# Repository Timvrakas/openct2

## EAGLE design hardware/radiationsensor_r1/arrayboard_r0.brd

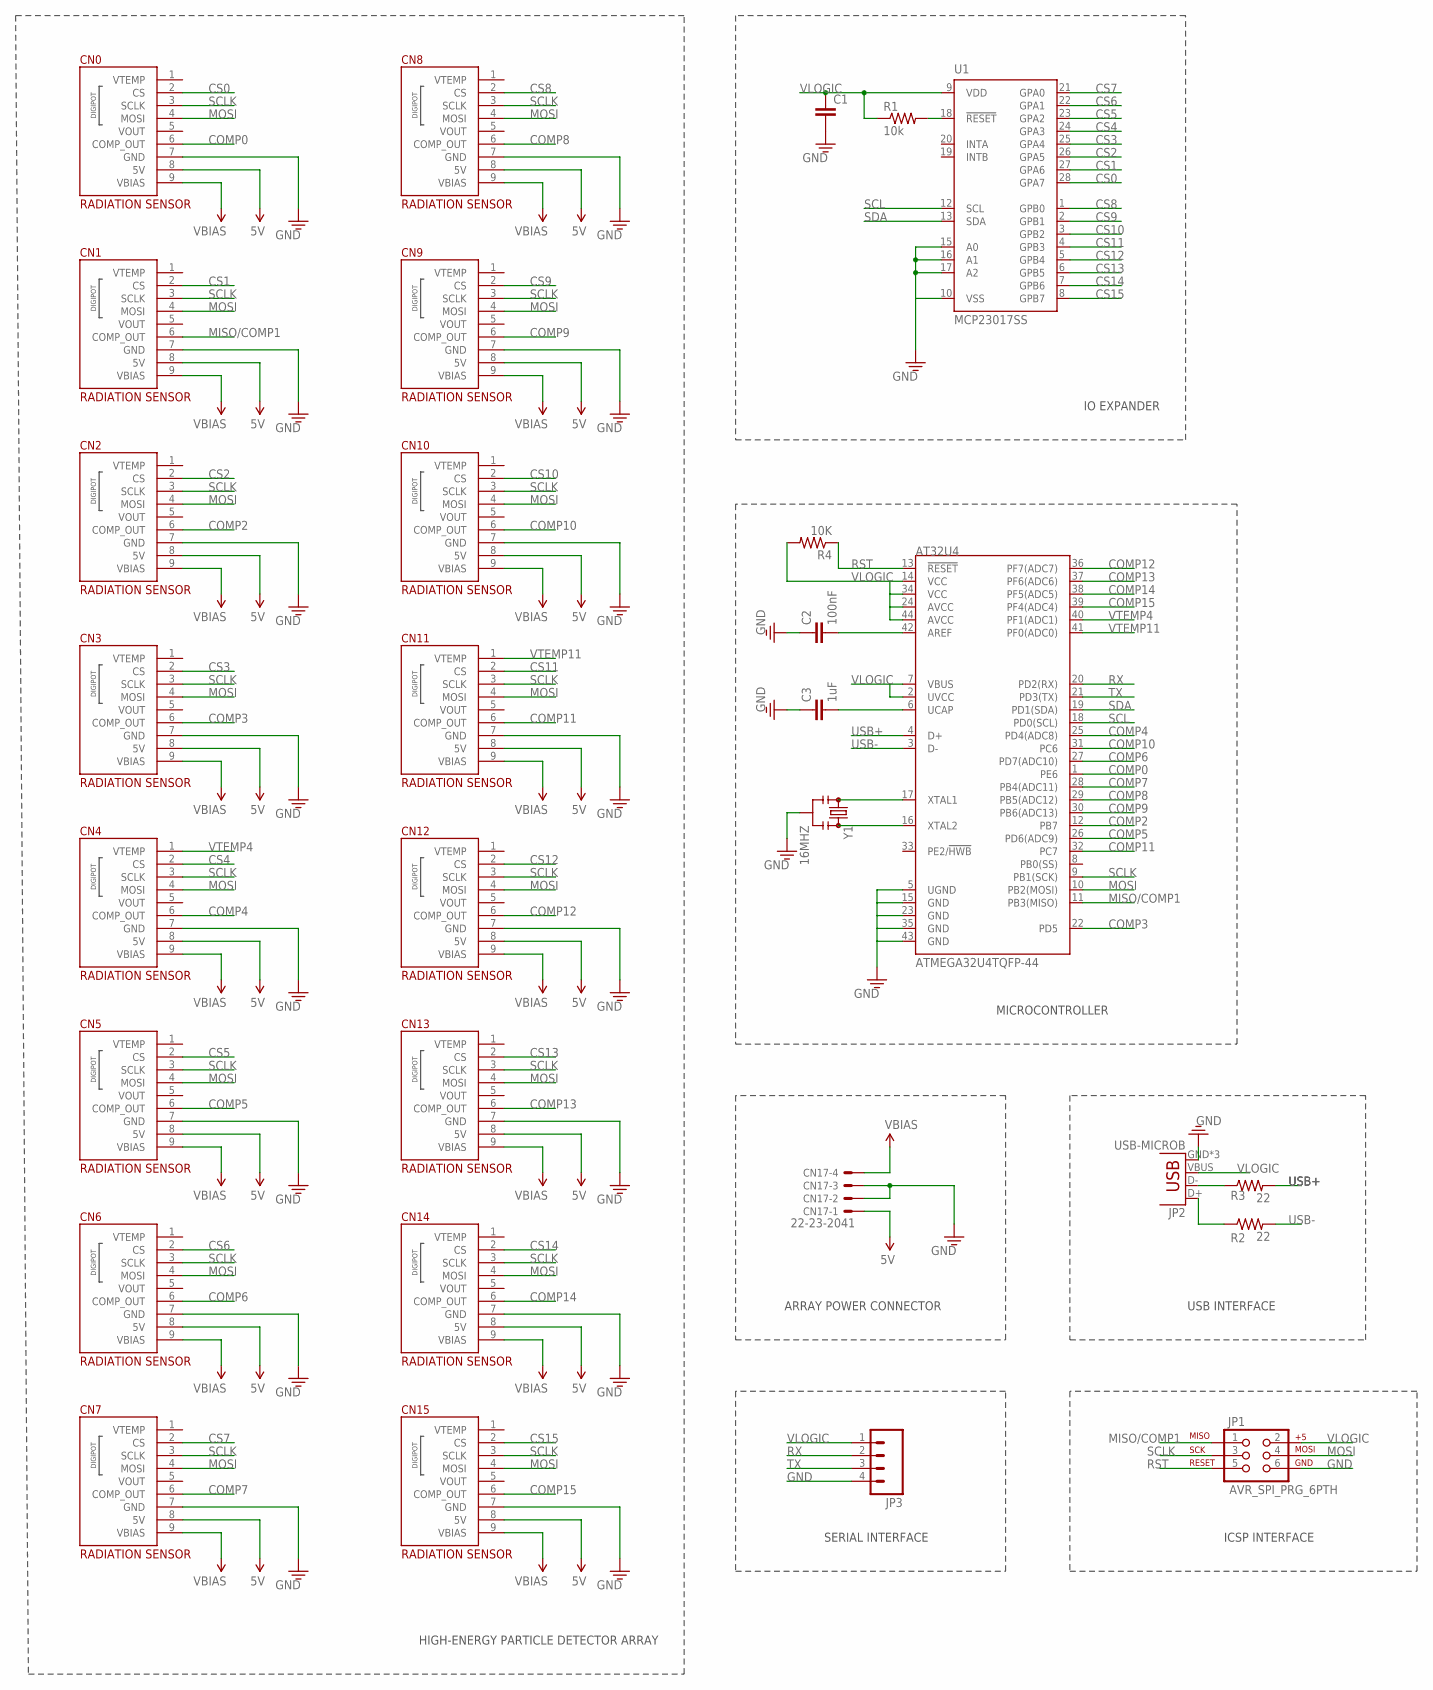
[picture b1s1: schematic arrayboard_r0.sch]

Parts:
AT32U4: ATMEGA32U4TQFP-44; TQFP44
C1: CAP0603; 0603
C2: 100nF; 0805
C3: 1uF; 0805
CN0, CN1, CN2, CN3, CN4, CN5, CN6, CN7, CN8, CN9, CN10, CN11, CN12, CN13, CN14, CN15: RADIATION-SENSOR-REV1
CN17: 22-23-2041
JP1: AVR_SPI_PRG_6PTH; 2X3
JP2: USB-MICROB
JP3: M04POLAR; MOLEX-1X4
R1: 10k; 0603
R2, R3: 22; 0805
R4: 10K; 0805
U1: MCP23017SS; SSOP28
Y1: 16MHZ; RESONATOR-SMD

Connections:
5V: CN0.8 (5V), CN1.8 (5V), CN2.8 (5V), CN3.8 (5V), CN4.8 (5V), CN5.8 (5V), CN6.8 (5V), CN7.8 (5V), CN8.8 (5V), CN9.8 (5V), CN10.8 (5V), CN11.8 (5V), CN12.8 (5V), CN13.8 (5V), CN14.8 (5V), CN15.8 (5V), CN17.1
COMP0: AT32U4.1 (PE6), CN0.6 (COMP_OUT)
COMP2: AT32U4.12 (PB7), CN2.6 (COMP_OUT)
COMP3: AT32U4.22 (PD5), CN3.6 (COMP_OUT)
COMP4: AT32U4.25 (PD4(ADC8)), CN4.6 (COMP_OUT)
COMP5: AT32U4.26 (PD6(ADC9)), CN5.6 (COMP_OUT)
COMP6: AT32U4.27 (PD7(ADC10)), CN6.6 (COMP_OUT)
COMP7: AT32U4.28 (PB4(ADC11)), CN7.6 (COMP_OUT)
COMP8: AT32U4.29 (PB5(ADC12)), CN8.6 (COMP_OUT)
COMP9: AT32U4.30 (PB6(ADC13)), CN9.6 (COMP_OUT)
COMP10: AT32U4.31 (PC6), CN10.6 (COMP_OUT)
COMP11: AT32U4.32 (PC7), CN11.6 (COMP_OUT)
COMP12: AT32U4.36 (PF7(ADC7)), CN12.6 (COMP_OUT)
COMP13: AT32U4.37 (PF6(ADC6)), CN13.6 (COMP_OUT)
COMP14: AT32U4.38 (PF5(ADC5)), CN14.6 (COMP_OUT)
COMP15: AT32U4.39 (PF4(ADC4)), CN15.6 (COMP_OUT)
CS0: CN0.2 (CS), U1.28 (GPA7)
CS1: CN1.2 (CS), U1.27 (GPA6)
CS2: CN2.2 (CS), U1.26 (GPA5)
CS3: CN3.2 (CS), U1.25 (GPA4)
CS4: CN4.2 (CS), U1.24 (GPA3)
CS5: CN5.2 (CS), U1.23 (GPA2)
CS6: CN6.2 (CS), U1.22 (GPA1)
CS7: CN7.2 (CS), U1.21 (GPA0)
CS8: CN8.2 (CS), U1.1 (GPB0)
CS9: CN9.2 (CS), U1.2 (GPB1)
CS10: CN10.2 (CS), U1.3 (GPB2)
CS11: CN11.2 (CS), U1.4 (GPB3)
CS12: CN12.2 (CS), U1.5 (GPB4)
CS13: CN13.2 (CS), U1.6 (GPB5)
CS14: CN14.2 (CS), U1.7 (GPB6)
CS15: CN15.2 (CS), U1.8 (GPB7)
GND: AT32U4.5 (UGND), AT32U4.15 (GND), AT32U4.23 (GND), AT32U4.35 (GND), AT32U4.43 (GND), C1.2, C2.1, C3.1, CN0.7 (GND), CN1.7 (GND), CN2.7 (GND), CN3.7 (GND), CN4.7 (GND), CN5.7 (GND), CN6.7 (GND), CN7.7 (GND), CN8.7 (GND), CN9.7 (GND), CN10.7 (GND), CN11.7 (GND), CN12.7 (GND), CN13.7 (GND), CN14.7 (GND), CN15.7 (GND), CN17.2, CN17.3, JP1.6, JP2.GND, JP2.MT1 (GND), JP2.MT2 (GND), JP3.4, U1.10 (VSS), U1.15 (A0), U1.16 (A1), U1.17 (A2), Y1.2
MISO/COMP1: AT32U4.11 (PB3(MISO)), CN1.6 (COMP_OUT), JP1.1
MOSI: AT32U4.10 (PB2(MOSI)), CN0.4 (MOSI), CN1.4 (MOSI), CN2.4 (MOSI), CN3.4 (MOSI), CN4.4 (MOSI), CN5.4 (MOSI), CN6.4 (MOSI), CN7.4 (MOSI), CN8.4 (MOSI), CN9.4 (MOSI), CN10.4 (MOSI), CN11.4 (MOSI), CN12.4 (MOSI), CN13.4 (MOSI), CN14.4 (MOSI), CN15.4 (MOSI), JP1.4
unnamed: JP2.D-, R3.1
unnamed: R1.2, U1.18 (!RESET)
unnamed: JP2.D+, R2.1
unnamed: AT32U4.6 (UCAP), C3.2
unnamed: AT32U4.17 (XTAL1), Y1.1
unnamed: AT32U4.16 (XTAL2), Y1.3
unnamed: AT32U4.42 (AREF), C2.2
RST: AT32U4.13 (!RESET), JP1.5, R4.1
RX: AT32U4.20 (PD2(RX)), JP3.2
SCL: AT32U4.18 (PD0(SCL)), U1.12 (SCL)
SCLK: AT32U4.9 (PB1(SCK)), CN0.3 (SCLK), CN1.3 (SCLK), CN2.3 (SCLK), CN3.3 (SCLK), CN4.3 (SCLK), CN5.3 (SCLK), CN6.3 (SCLK), CN7.3 (SCLK), CN8.3 (SCLK), CN9.3 (SCLK), CN10.3 (SCLK), CN11.3 (SCLK), CN12.3 (SCLK), CN13.3 (SCLK), CN14.3 (SCLK), CN15.3 (SCLK), JP1.3
SDA: AT32U4.19 (PD1(SDA)), U1.13 (SDA)
TX: AT32U4.21 (PD3(TX)), JP3.3
USB+: AT32U4.4 (D+), R3.2
USB-: AT32U4.3 (D-), R2.2
VBIAS: CN0.9 (VBIAS), CN1.9 (VBIAS), CN2.9 (VBIAS), CN3.9 (VBIAS), CN4.9 (VBIAS), CN5.9 (VBIAS), CN6.9 (VBIAS), CN7.9 (VBIAS), CN8.9 (VBIAS), CN9.9 (VBIAS), CN10.9 (VBIAS), CN11.9 (VBIAS), CN12.9 (VBIAS), CN13.9 (VBIAS), CN14.9 (VBIAS), CN15.9 (VBIAS), CN17.4
VLOGIC: AT32U4.7 (VBUS), AT32U4.14 (VCC), AT32U4.24 (AVCC), AT32U4.34 (VCC), AT32U4.44 (AVCC), C1.1, JP1.2, JP2.VBUS, JP3.1, R1.1, R4.2, U1.9 (VDD)
VTEMP4: AT32U4.40 (PF1(ADC1)), CN4.1 (VTEMP)
VTEMP11: AT32U4.41 (PF0(ADC0)), CN11.1 (VTEMP)

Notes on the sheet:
HIGH-ENERGY PARTICLE DETECTOR ARRAY
ARRAY POWER CONNECTOR
MICROCONTROLLER
IO EXPANDER
USB INTERFACE
SERIAL INTERFACE
ICSP INTERFACE

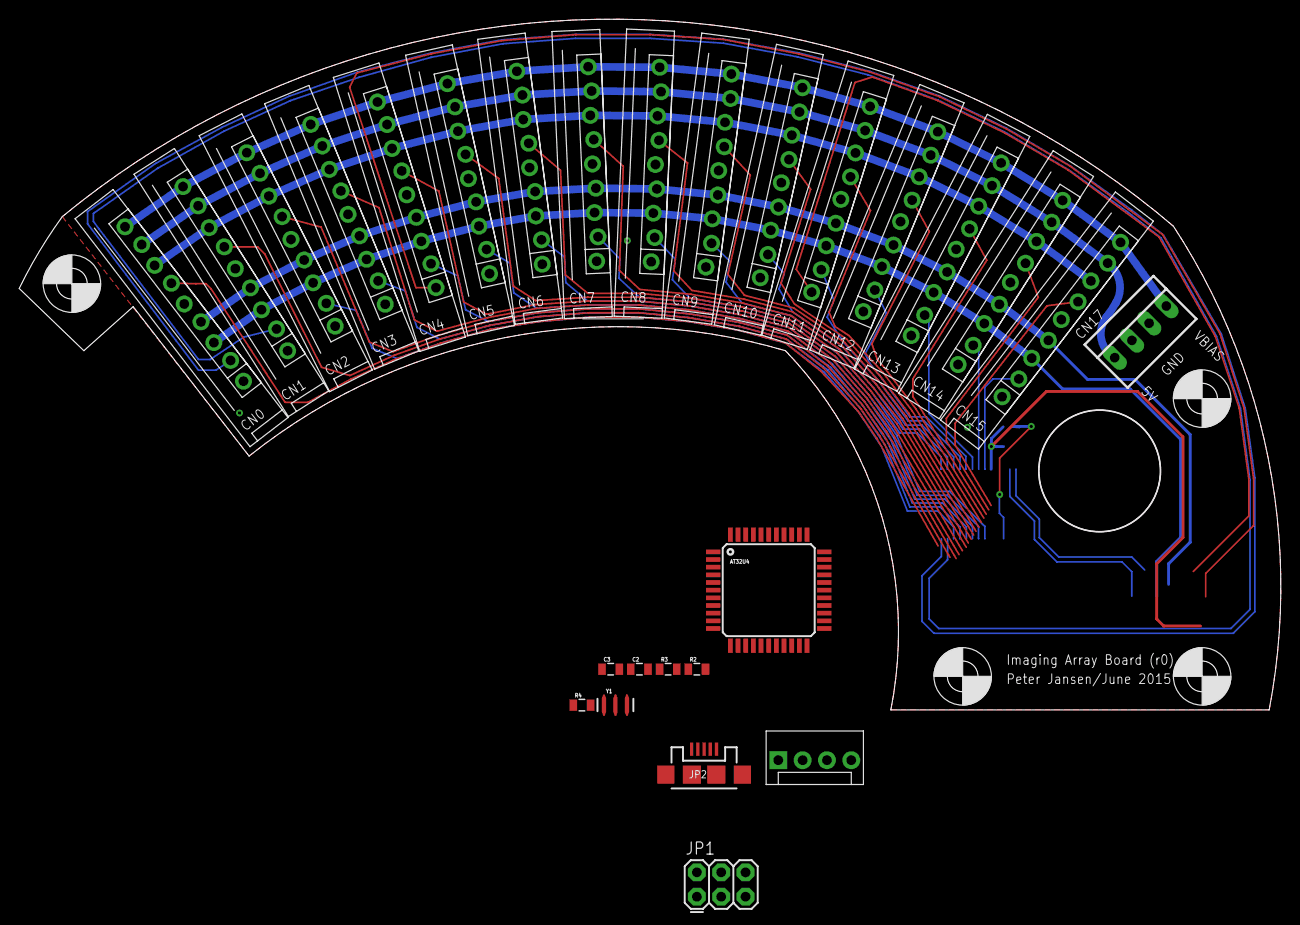
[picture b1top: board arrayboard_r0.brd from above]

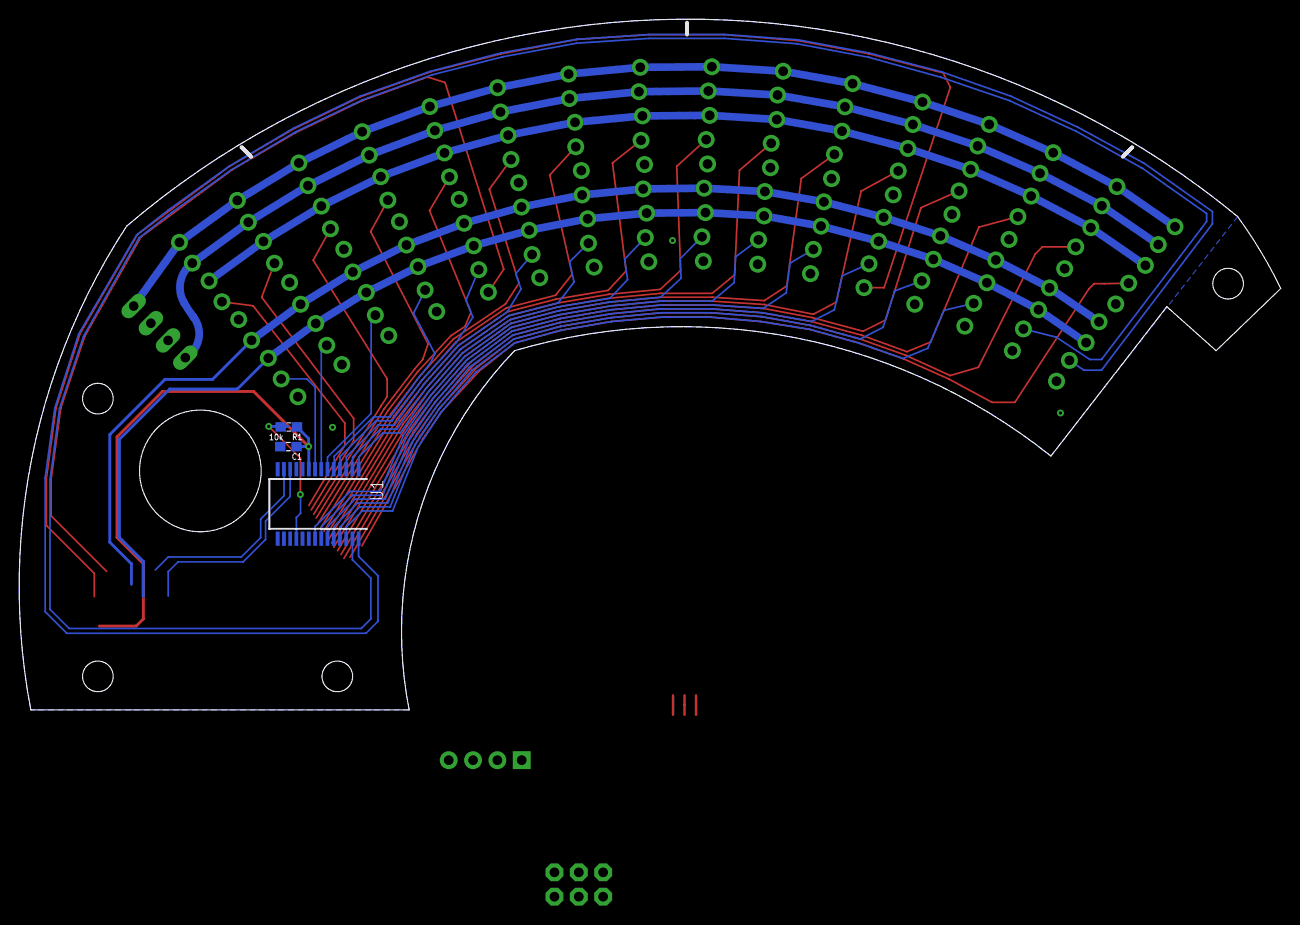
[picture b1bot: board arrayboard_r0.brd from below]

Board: 2 copper layers, 131.7 x 72.1 mm, 34 parts (3 on the bottom side), 54 nets.

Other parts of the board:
U$35, U$36, U$37, U$38: MOUNT-M3

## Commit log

2015-07-07 Added MCU to Array board

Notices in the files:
parts and their libraries:
openct: Licensing: Creative Commons ShareAlike 4.0 International - https://creativecommons.org/licenses/by-sa/4.0
